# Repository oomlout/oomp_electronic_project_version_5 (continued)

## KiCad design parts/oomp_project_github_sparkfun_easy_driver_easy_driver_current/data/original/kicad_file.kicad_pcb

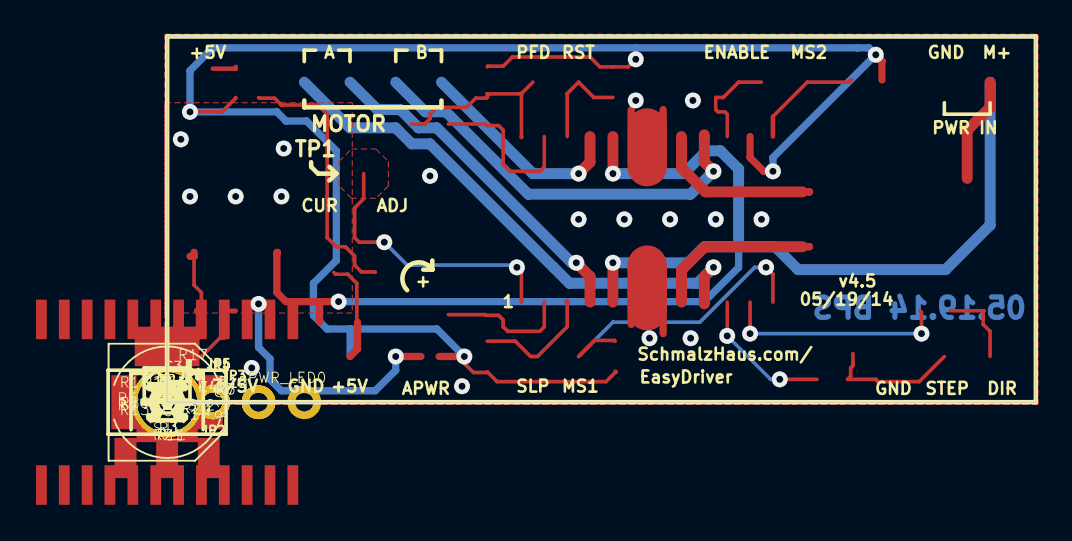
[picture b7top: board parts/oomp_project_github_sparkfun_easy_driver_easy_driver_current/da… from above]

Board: 2 copper layers, 48.3 x 20.3 mm, 47 parts (1 on the bottom side), 27 nets.

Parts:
C1: .1uF; 0603-CAP
C2: 1uf; 0603-CAP
C3: 47uF; PANASONIC_D
C4, C5: 680pF; 0603-CAP
FID1, FID2: FIDUCIAL1X2; FIDUCIAL-1X2
FRAME2: FRAME-LETTER; CREATIVE_COMMONS
IC1: A3967SLB; SO24W
IC2: V_REG_317SMD; SOT223
JP1, JP4, JP5, JP6, JP7: 1X02_NO_SILK
JP2: 1X03_NO_SILK
JP3: 1X04_NO_SILK
JP8, JP9: STAND-OFF
LOGO1: OSHW-LOGOS; OSHW-LOGO-S
PWR_LED0: YELLOW; LED-0603
R1, R2: .75; 0805
R3, R4: 20K; 0603-RES
R5: 2.49K; 0603-RES
R6: 390; 0603-RES
R7: 330; 0603-RES
R8: 240; 0603-RES
R9, R18, R19: 1K; 0603-RES
R10, R11, R12, R13, R14, R15, R20, R21: 10K; 0603-RES
R16: 10K; TRIMPOT-3MM-2
R17: 6.8K; 0603-RES
SJ1: SOLDERJUMPERTRACE; SJ_2S-TRACE
SJ2: SOLDERJUMPERNO; SJ_2S-NO
TP1: TEST-POINTTP_15TH_THRU; TP_15TH
U$1: SCHMALZHAUS_SMALL
U$2: LOGO-SFENEW; SFE-NEW-WEBLOGO

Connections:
5V_ALT: IC2.2, IC2.4, R8.2, SJ1.1
DIR: IC1.11, R18.1
DIR_IN: JP2.3, R18.2, R20.2
ENABLE: IC1.15, JP6.1, R13.2
GND: C1.2, C2.2, C3.-, C4.2, C5.2, IC1.6, IC1.7, IC1.18, IC1.19, JP1.1, JP2.1, JP4.2, PWR_LED0.C, R1.1, R2.1, R3.1, R4.1, R5.1, R7.1, R13.1, R17.1, R20.1, R21.1, SJ2.2
MS1: IC1.12, JP5.1, R14.1
MS2: IC1.13, JP6.2, R10.1
unnamed: IC1.8, R1.2
unnamed: PWR_LED0.A, R9.1
unnamed: IC1.17, R2.2
unnamed: R6.1, R7.2, SJ2.1
unnamed: C4.1, IC1.2, R3.2
unnamed: IC2.1, R6.2, R8.1
unnamed: C5.1, IC1.23, R4.2
unnamed: R5.2, R16.3
OUT1A: IC1.16, JP3.3
OUT1B: IC1.21, JP3.4
OUT2A: IC1.9, JP3.1
OUT2B: IC1.4, JP3.2
PFD: IC1.24, JP7.1, R12.1, R17.2
RESET: IC1.22, JP7.2, R15.1
SLEEP: IC1.3, JP5.2, R11.1
STEP: IC1.10, R19.1
STEP_IN: JP2.2, R19.2, R21.2
V+: C1.1, C3.+, IC1.5, IC1.20, IC2.3, JP1.2
VCC: C2.1, IC1.14, JP4.1, R9.2, R10.2, R11.2, R12.2, R14.2, R15.2, R16.1, SJ1.2
VREF: IC1.1, R16.2, TP1.P$1

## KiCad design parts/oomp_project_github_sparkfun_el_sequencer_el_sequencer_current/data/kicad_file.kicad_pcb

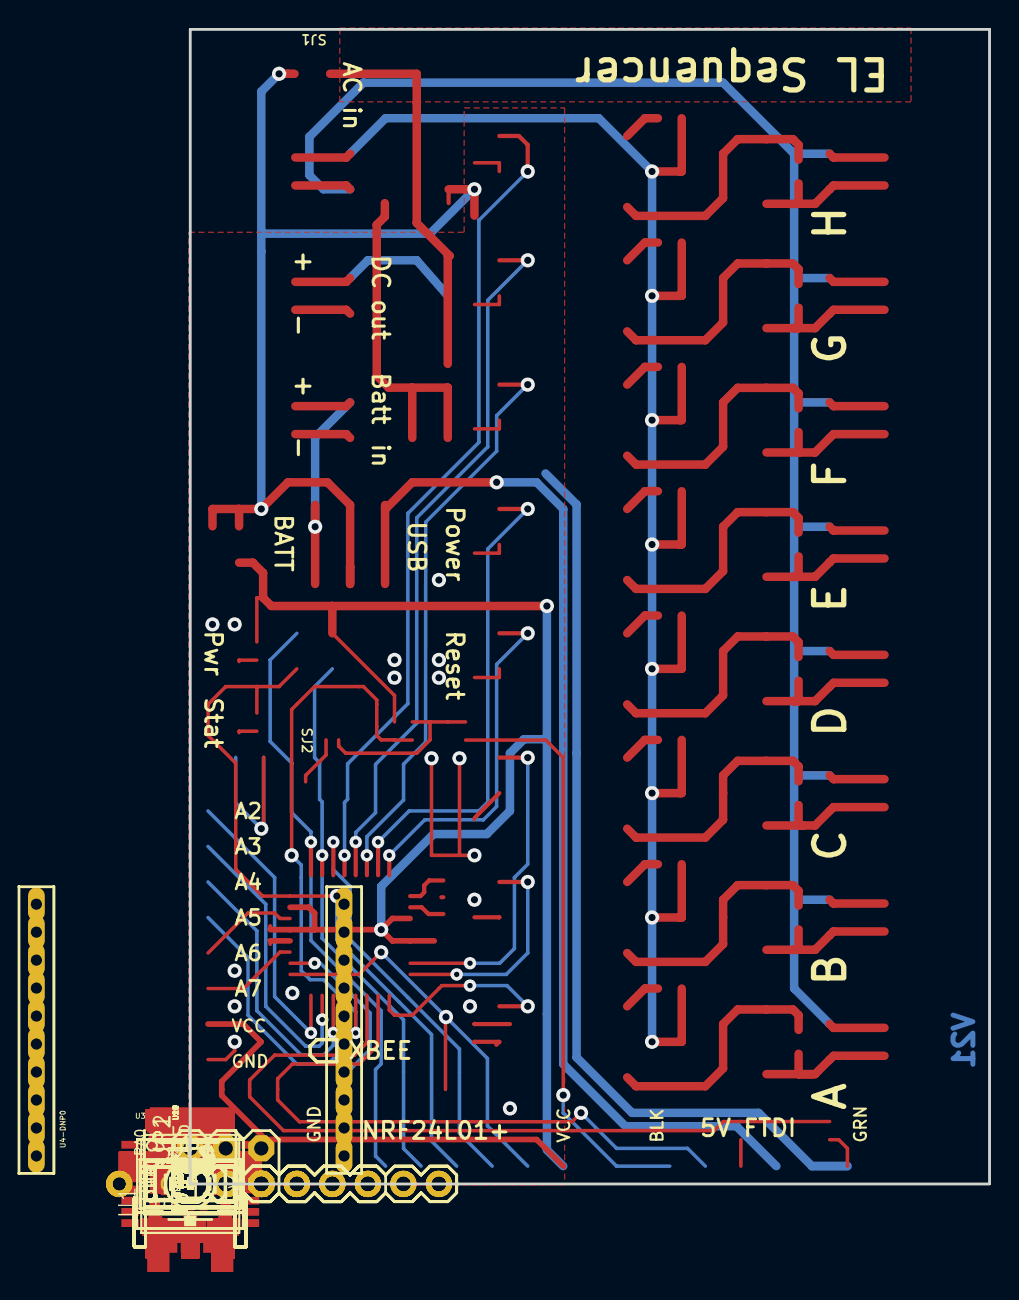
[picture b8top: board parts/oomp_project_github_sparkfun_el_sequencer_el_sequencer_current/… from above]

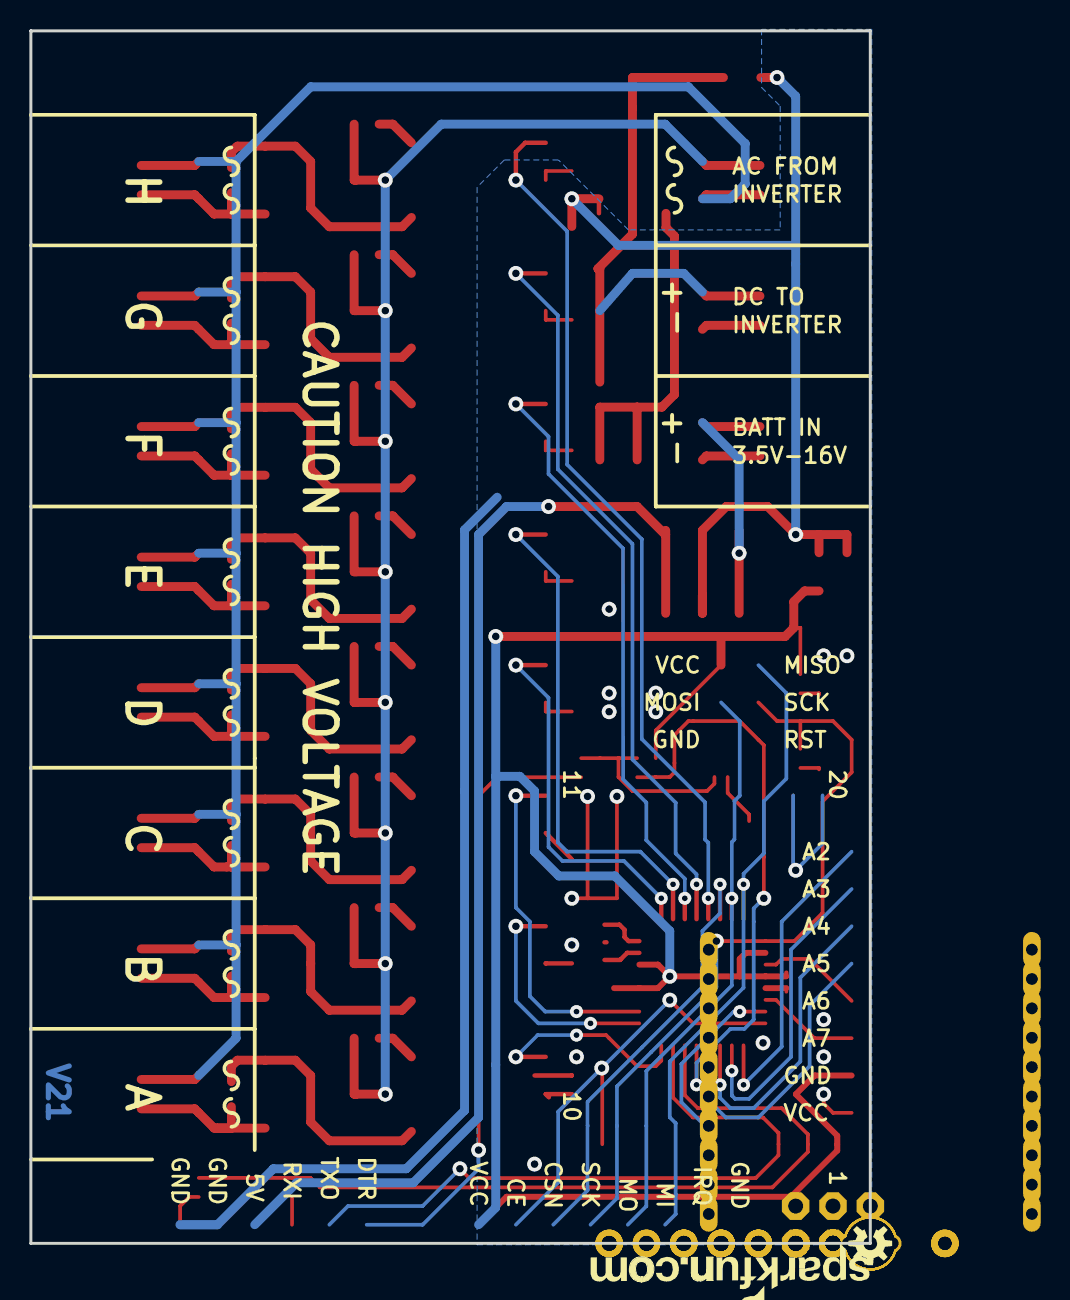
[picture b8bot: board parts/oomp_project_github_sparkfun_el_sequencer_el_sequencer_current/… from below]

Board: 2 copper layers, 57.1 x 82.5 mm, 106 parts (2 on the bottom side), 72 nets.

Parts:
C1, C4, C5, C6, C7: 0.1uF; 0402-CAP
C2, C3: 10uF; EIA3216
FRAME1, FRAME2: FRAME-LETTER; CREATIVE_COMMONS
J1: Battery; JST-2-SMD
J2: DC-OUTPUT; JST-2-SMD
J3: AC-INPUT; JST-2-SMD
J4, J5, J6, J7, J8, J9, J10, J11: JST-2-SMD
JP1, JP6, JP7, JP9, JP10, JP11, JP12, JP13, JP14, JP15, JP16: 1X02
JP2: I/O; 1X08_ROUND
JP3: 5V_FTDI; 1X06
JP4: nRF24L01; 1X08
JP5: PROG; 2X3
JP8: LOGO-SFESK; SFE-LOGO-FLAME
LED1: Power; LED-0603
LED2: Status; LED-0603
R1: 390; 0603-RES
R2: 240; 0603-RES
R3, R5, R7, R9: 1K; 0402-RES
R4, R6: 2K; 0402-RES
R8: 10K; 0402-RES
R10, R11, R12, R13, R22, R23, R24, R25: 390; 0402-RES
R14, R15, R16, R17, R18, R19, R20, R21, R26, R27, R28, R29, R30, R31, R32, R33: 330; 0603-RES
RA0: A; AXIAL-0.4
RB0: B; AXIAL-0.4
S1: POWER; AYZ0202
S2: RESET; TACTILE_SWITCH_SMD
SJ1: SJ_ROUND
SJ2: SJ_2S-NO
U1: LM317; V-REG_DPACK
U2: MIC5219-3.3; SOT23-5
U3: ATMEGA328P; TQFP32-08
U4-DNP0: XBEE HEADER; XBEE-LONGPAD
U5, U6, U7, U8, U13, U14, U15, U16: MOC3063S; DIP8SMD
U9, U10, U11, U12, U17, U18, U19, U20: Z0103MN; SOT223
U$1: OSHW-LOGOS; OSHW-LOGO-S
U$2: LOGO-SFENEW; SFE-NEW-WEBLOGO
U$3, U$4: FIDUCIALUFIDUCIAL; MICRO-FIDUCIAL
U$5, U$6, U$7, U$8: STAND-OFF
Y1: 8MHz; RESONATOR-SMD

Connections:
5VUSB: JP3.4, S1.3, S1.6
ADC_2: JP2.8, U3.25
ADC_3: JP2.7, U3.26
ADC_4: JP2.6, U3.27
ADC_5: JP2.5, U3.28
ADC_6*: JP2.4, U3.19
ADC_7*: JP2.3, U3.22
CE/SLEEP: JP4.7, U3.24, U4-DNP0.9
CSN: JP4.6, U3.14
DTR: C5.1, R5.1, R6.2, SJ2.2
EL_A: U3.32, U5.1
EL_B: U3.1, U6.1
EL_C: U3.2, U7.1
EL_D: U3.9, U8.1
EL_E: U3.10, U13.1
EL_F: U3.11, U14.1
EL_G: U3.12, U15.1
EL_H: U3.13, U16.1
FTDI_DTR: JP3.1, R5.2
FTDI_RXI: JP3.3, R3.2
GND: C1.2, C2.C, C3.C, C4.2, C6.2, C7.2, J1.1, J2.1, JP1.1, JP2.1, JP3.5, JP3.6, JP4.1, JP5.6, JP6.2, LED1.C, LED2.C, R1.1, R4.1, R6.1, R10.1, R11.1, R12.1, R13.1, R22.1, R23.1, R24.1, R25.1, RB0.P$1, S2.3, U2.2, U3.3, U3.5, U3.21, U4-DNP0.10, Y1.2
HV: J3.2, JP7.1, R14.2, R16.2, R18.2, R20.2, R26.2, R28.2, R30.2, R32.2, U9.4, U10.4, U11.4, U12.4, U17.4, U18.4, U19.4, U20.4
HVGND: J3.1, J4.1, J5.1, J6.1, J7.1, J8.1, J9.1, J10.1, J11.1, JP7.2, JP9.1, JP10.1, JP11.1, JP12.1, JP13.1, JP14.1, JP15.1, JP16.1
INV: C2.A, J2.2, JP6.1, R2.2, RA0.P$2, SJ1.2, U1.4
IRQ: JP4.2, U3.23
MISO: JP4.3, JP5.1, U3.16
MOSI: JP4.4, JP5.4, U3.15
unnamed: U3.7, Y1.1
unnamed: R17.1, U6.4, U10.3
unnamed: R11.2, U6.2
unnamed: LED1.A, R7.1
unnamed: R16.1, U6.6
unnamed: U3.8, Y1.3
unnamed: R10.2, U5.2
unnamed: SJ2.1, U4-DNP0.17
unnamed: J5.2, JP10.2, R17.2, U10.1
unnamed: R19.1, U7.4, U11.3
unnamed: R14.1, U5.6
unnamed: R12.2, U7.2
unnamed: R1.2, R2.1, RA0.P$1, RB0.P$2, U1.1
unnamed: LED2.A, R9.1
unnamed: R18.1, U7.6
unnamed: J6.2, JP11.2, R19.2, U11.1
unnamed: R21.1, U8.4, U12.3
unnamed: R13.2, U8.2
unnamed: R20.1, U8.6
unnamed: J7.2, JP12.2, R21.2, U12.1
unnamed: J4.2, JP9.2, R15.2, U9.1
unnamed: R27.1, U13.4, U17.3
unnamed: R22.2, U13.2
unnamed: R26.1, U13.6
unnamed: J8.2, JP13.2, R27.2, U17.1
unnamed: R29.1, U14.4, U18.3
unnamed: R23.2, U14.2
unnamed: R28.1, U14.6
unnamed: J9.2, JP14.2, R29.2, U18.1
unnamed: R31.1, U15.4, U19.3
unnamed: R24.2, U15.2
unnamed: R30.1, U15.6
unnamed: J10.2, JP15.2, R31.2, U19.1
unnamed: R33.1, U16.4, U20.3
unnamed: R25.2, U16.2
unnamed: R32.1, U16.6
unnamed: J11.2, JP16.2, R33.2, U20.1
unnamed: R15.1, U5.4, U9.3
RAW: C1.1, S1.2, S1.5, SJ1.1, U1.3, U2.1, U2.3
RST: C5.2, JP5.5, R8.1, S2.1, U3.29
RXI: R3.1, R4.2, U3.30, U4-DNP0.2
SCK: JP4.5, JP5.3, R9.2, U3.17
TXO: JP3.2, U3.31, U4-DNP0.3
VBATT: J1.2, JP1.2, S1.1, S1.4
VCC: C3.A, C4.1, C6.1, C7.1, JP2.2, JP4.8, JP5.2, R7.2, R8.2, U2.5, U3.4, U3.6, U3.18, U3.20, U4-DNP0.1
